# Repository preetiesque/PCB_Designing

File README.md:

# PCB_Designing
Repository consisting of tutorials for PCB Design in Documentation Format and Codes.(Gcodes and Gerber Files)
PCB stands for Printed Circuit Board.
Software used - EAGLE and Flatcam.

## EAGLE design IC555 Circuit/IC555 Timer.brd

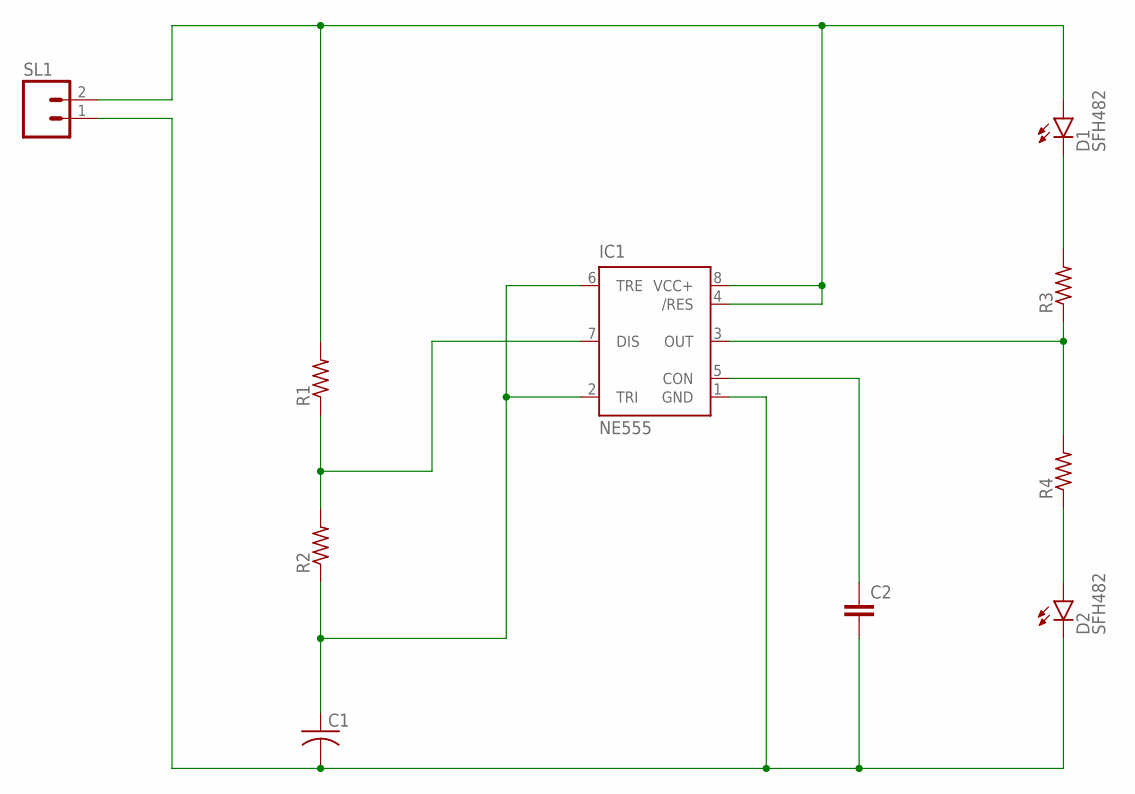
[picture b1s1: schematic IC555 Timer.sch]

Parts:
C1: C-US025-030X050; C025-030X050
C2: C-EU025-024X044; C025-024X044
D1, D2: SFH482
IC1: NE555; DIL-08
R1, R2, R3, R4: R-US_0204/5; 0204/5
SL1: M02; 02P

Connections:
unnamed: IC1.7 (DIS), R1.1, R2.2
unnamed: C1.1, IC1.2 (TRI), IC1.6 (TRE), R2.1
unnamed: D1.A, IC1.4 (/RES), IC1.8 (VCC+), R1.2, SL1.2
unnamed: C1.2, C2.2, D2.K (C), IC1.1 (GND), SL1.1
unnamed: D1.K (C), R3.2
unnamed: IC1.3 (OUT), R3.1, R4.2
unnamed: D2.A, R4.1
unnamed: C2.1, IC1.5 (CON)

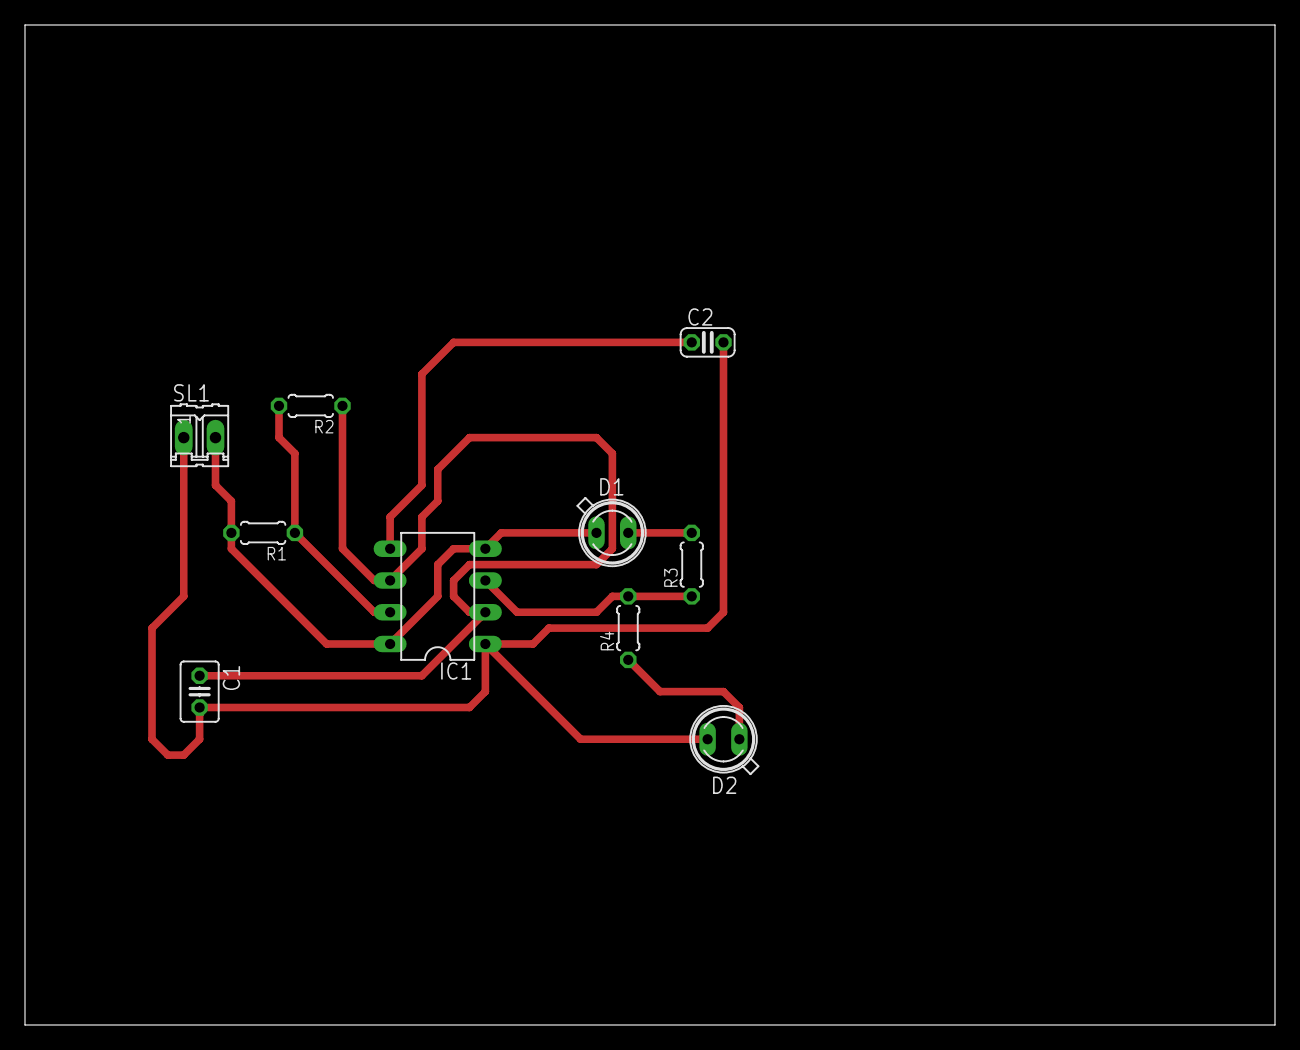
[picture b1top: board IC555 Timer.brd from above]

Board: 2 copper layers, 100.0 x 80.0 mm, 10 parts (0 on the bottom side), 8 nets.

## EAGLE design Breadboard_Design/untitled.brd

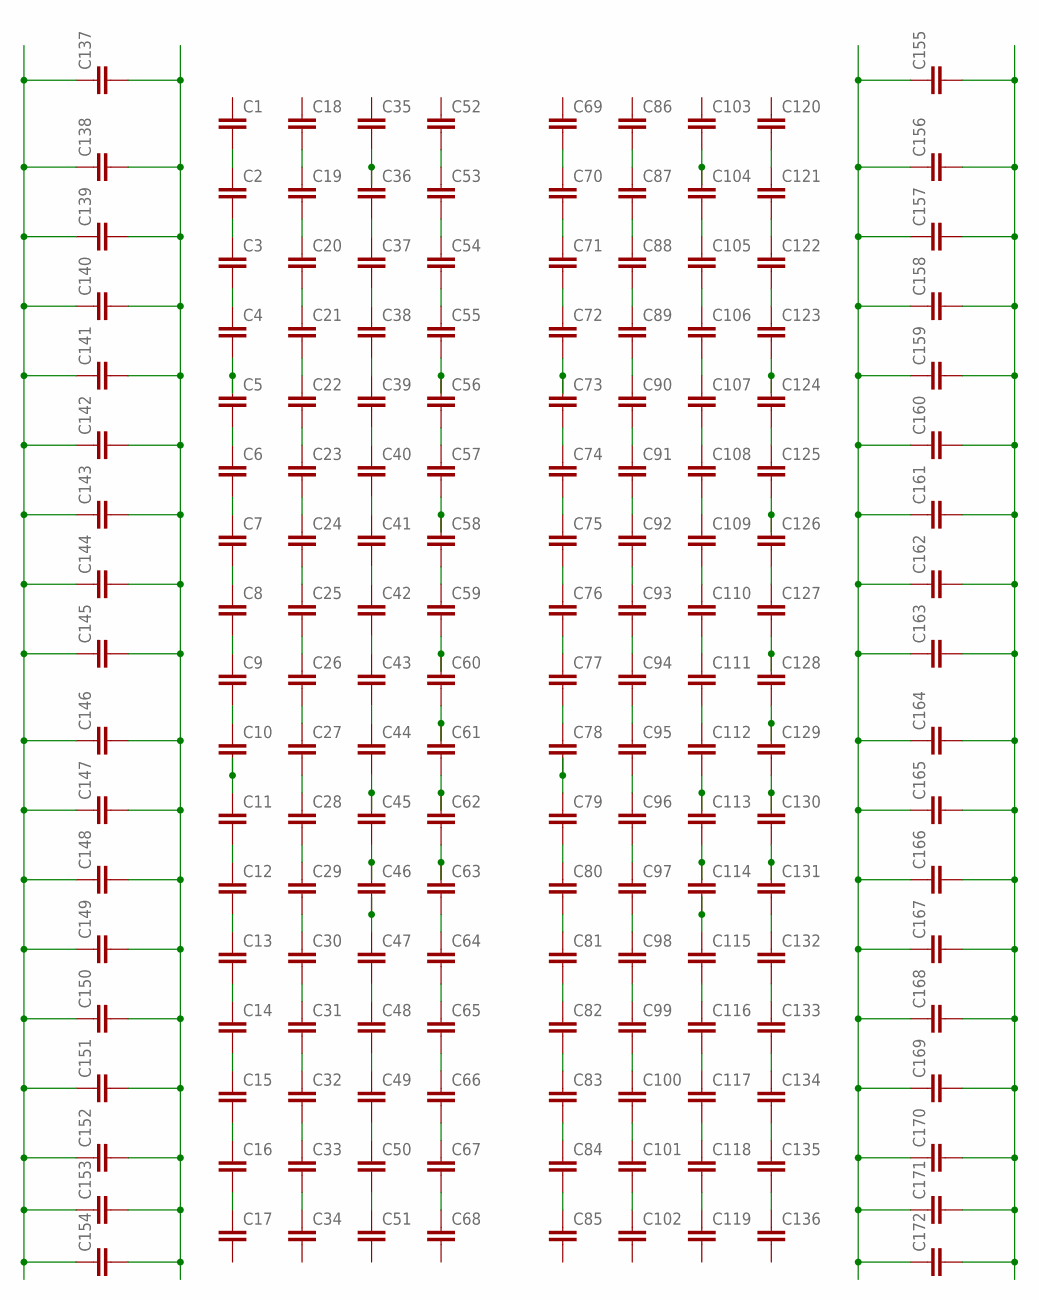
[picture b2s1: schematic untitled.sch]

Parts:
C1, C2, C3, C4, C5, C6, C7, C8, C9, C10, C11, C12, C13, C14, C15, C16, C17, C18, C19, C20, C21, C22, C23, C24, C25, C26, C27, C28, C29, C30, C31, C32, C33, C34, C35, C36, C37, C38, C39, C40, C41, C42, C43, C44, C45, C46, C47, C48, C49, C50, C51, C52, C53, C54, C55, C56, C57, C58, C59, C60, C61, C62, C63, C64, C65, C66, C67, C68, C69, C70, C71, C72, C73, C74, C75, C76, C77, C78, C79, C80, C81, C82, C83, C84, C85, C86, C87, C88, C89, C90, C91, C92, C93, C94, C95, C96, C97, C98, C99, C100, C101, C102, C103, C104, C105, C106, C107, C108, C109, C110, C111, C112, C113, C114, C115, C116, C117, C118, C119, C120, C121, C122, C123, C124, C125, C126, C127, C128, C129, C130, C131, C132, C133, C134, C135, C136, C137, C138, C139, C140, C141, C142, C143, C144, C145, C146, C147, C148, C149, C150, C151, C152, C153, C154, C155, C156, C157, C158, C159, C160, C161, C162, C163, C164, C165, C166, C167, C168, C169, C170, C171, C172: C2,5-3; C2.5-3

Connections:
unnamed: C1.2, C2.1
unnamed: C2.2, C3.1
unnamed: C3.2, C4.1
unnamed: C4.2, C5.1
unnamed: C16.2, C17.1
unnamed: C15.2, C16.1
unnamed: C14.2, C15.1
unnamed: C13.2, C14.1
unnamed: C12.2, C13.1
unnamed: C11.2, C12.1
unnamed: C10.2, C11.1
unnamed: C5.2, C6.1
unnamed: C6.2, C7.1
unnamed: C7.2, C8.1
unnamed: C8.2, C9.1
unnamed: C9.2, C10.1
unnamed: C18.2, C19.1
unnamed: C19.2, C20.1
unnamed: C20.2, C21.1
unnamed: C21.2, C22.1
unnamed: C22.2, C23.1
unnamed: C23.2, C24.1
unnamed: C24.2, C25.1
unnamed: C25.2, C26.1
unnamed: C26.2, C27.1
unnamed: C27.2, C28.1
unnamed: C28.2, C29.1
unnamed: C29.2, C30.1
unnamed: C30.2, C31.1
unnamed: C47.2, C48.1
unnamed: C46.2, C47.1
unnamed: C40.2, C41.1
unnamed: C41.2, C42.1
unnamed: C42.2, C43.1
unnamed: C43.2, C44.1
unnamed: C44.2, C45.1
unnamed: C45.2, C46.1
unnamed: C52.2, C53.1
unnamed: C53.2, C54.1
unnamed: C54.2, C55.1
unnamed: C55.2, C56.1
unnamed: C56.2, C57.1
unnamed: C57.2, C58.1
unnamed: C58.2, C59.1
unnamed: C59.2, C60.1
unnamed: C60.2, C61.1
unnamed: C61.2, C62.1
unnamed: C62.2, C63.1
unnamed: C63.2, C64.1
unnamed: C64.2, C65.1
unnamed: C35.2, C36.1
unnamed: C31.2, C32.1
unnamed: C48.2, C49.1
unnamed: C65.2, C66.1
unnamed: C33.2, C34.1
unnamed: C32.2, C33.1
unnamed: C49.2, C50.1
unnamed: C66.2, C67.1
unnamed: C67.2, C68.1
unnamed: C50.2, C51.1
unnamed: C37.2, C38.1
unnamed: C36.2, C37.1
unnamed: C38.2, C39.1
unnamed: C39.2, C40.1
unnamed: C69.2, C70.1
unnamed: C70.2, C71.1
unnamed: C71.2, C72.1
unnamed: C72.2, C73.1
unnamed: C84.2, C85.1
unnamed: C83.2, C84.1
unnamed: C82.2, C83.1
unnamed: C81.2, C82.1
unnamed: C80.2, C81.1
unnamed: C79.2, C80.1
unnamed: C78.2, C79.1
unnamed: C73.2, C74.1
unnamed: C74.2, C75.1
unnamed: C75.2, C76.1
unnamed: C76.2, C77.1
unnamed: C77.2, C78.1
unnamed: C86.2, C87.1
unnamed: C87.2, C88.1
unnamed: C88.2, C89.1
unnamed: C89.2, C90.1
unnamed: C90.2, C91.1
unnamed: C91.2, C92.1
unnamed: C92.2, C93.1
unnamed: C93.2, C94.1
unnamed: C94.2, C95.1
unnamed: C95.2, C96.1
unnamed: C96.2, C97.1
unnamed: C97.2, C98.1
unnamed: C98.2, C99.1
unnamed: C115.2, C116.1
unnamed: C114.2, C115.1
unnamed: C108.2, C109.1
unnamed: C109.2, C110.1
unnamed: C110.2, C111.1
unnamed: C111.2, C112.1
unnamed: C112.2, C113.1
unnamed: C113.2, C114.1
unnamed: C120.2, C121.1
unnamed: C121.2, C122.1
unnamed: C122.2, C123.1
unnamed: C123.2, C124.1
unnamed: C124.2, C125.1
unnamed: C125.2, C126.1
unnamed: C126.2, C127.1
unnamed: C127.2, C128.1
unnamed: C128.2, C129.1
unnamed: C129.2, C130.1
unnamed: C130.2, C131.1
unnamed: C131.2, C132.1
unnamed: C132.2, C133.1
unnamed: C103.2, C104.1
unnamed: C99.2, C100.1
unnamed: C116.2, C117.1
unnamed: C133.2, C134.1
unnamed: C101.2, C102.1
unnamed: C100.2, C101.1
unnamed: C117.2, C118.1
unnamed: C134.2, C135.1
unnamed: C135.2, C136.1
unnamed: C118.2, C119.1
unnamed: C105.2, C106.1
unnamed: C104.2, C105.1
unnamed: C106.2, C107.1
unnamed: C107.2, C108.1
unnamed: C137.1, C138.1, C139.1, C140.1, C141.1, C142.1, C143.1, C144.1, C145.1, C146.1, C147.1, C148.1, C149.1, C150.1, C151.1, C152.1, C153.1, C154.1
unnamed: C155.1, C156.1, C157.1, C158.1, C159.1, C160.1, C161.1, C162.1, C163.1, C164.1, C165.1, C166.1, C167.1, C168.1, C169.1, C170.1, C171.1, C172.1
unnamed: C137.2, C138.2, C139.2, C140.2, C141.2, C142.2, C143.2, C144.2, C145.2, C146.2, C147.2, C148.2, C149.2, C150.2, C151.2, C152.2, C153.2, C154.2
unnamed: C155.2, C156.2, C157.2, C158.2, C159.2, C160.2, C161.2, C162.2, C163.2, C164.2, C165.2, C166.2, C167.2, C168.2, C169.2, C170.2, C171.2, C172.2

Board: 2 copper layers, 172 parts (0 on the bottom side), 132 nets, no tracks yet.

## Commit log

2022-04-01 Add files via upload
    Tutorial in form of documentation added.
2022-08-03 reverse-polarity-protection
2022-08-03 breadboard-design
2022-08-07 IC555-Circuit
